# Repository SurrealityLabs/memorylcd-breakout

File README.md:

# memorylcd-breakout
A very simple breakout board for Sharp memory LCDs

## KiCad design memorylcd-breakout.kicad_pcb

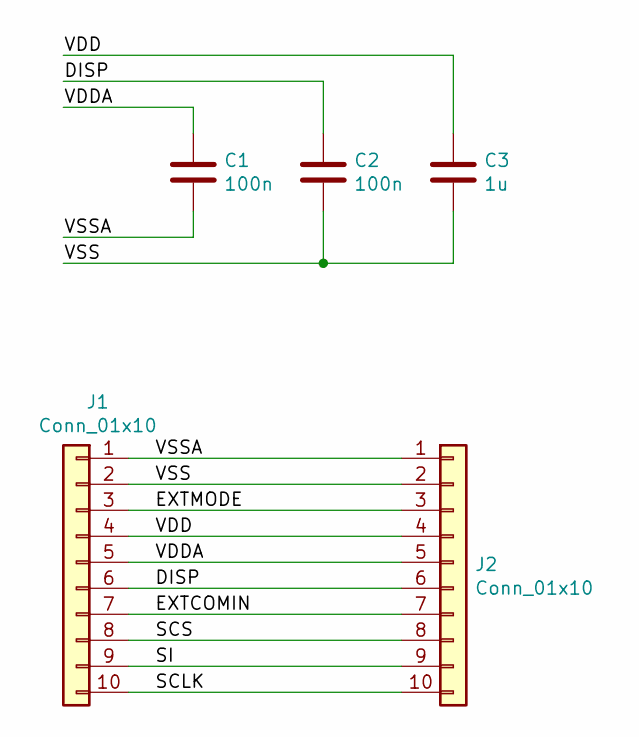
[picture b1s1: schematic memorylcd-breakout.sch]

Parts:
C1, C2: 100n; C_0603_1608Metric_Pad1.05x0.95mm_HandSolder
C3: 1u; C_0603_1608Metric_Pad1.05x0.95mm_HandSolder
J1: Conn_01x10; PinHeader_1x10_P2.54mm_Vertical
J2: Conn_01x10; TE_1-1734839-0_1x10-1MP_P0.5mm_Horizontal

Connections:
/DISP: C2.1, J1.6, J2.6
/EXTCOMIN: J1.7, J2.7
/EXTMODE: J1.3, J2.3
/SCLK: J1.10, J2.10
/SCS: J1.8, J2.8
/SI: J1.9, J2.9
/VDD: C3.1, J1.4, J2.4
/VDDA: C1.1, J1.5, J2.5
/VSS: C2.2, C3.2, J1.2, J2.2
/VSSA: C1.2, J1.1, J2.1

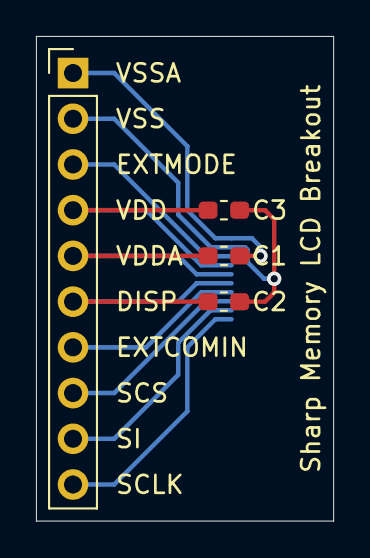
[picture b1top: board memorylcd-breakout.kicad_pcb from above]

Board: 2 copper layers, 16.5 x 26.9 mm, 5 parts (1 on the bottom side), 10 nets.

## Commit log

2021-03-23 Adding PCB
2021-03-27 Adding 3D printed bracket, to prevent flex cable from tearing on breadboard
